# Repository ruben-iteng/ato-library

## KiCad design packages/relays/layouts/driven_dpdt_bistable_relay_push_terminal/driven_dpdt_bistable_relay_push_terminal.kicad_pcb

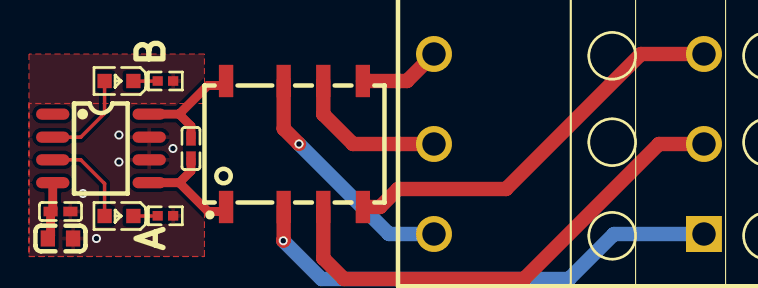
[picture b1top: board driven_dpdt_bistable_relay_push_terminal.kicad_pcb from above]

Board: 2 copper layers, 10 parts (0 on the bottom side), 14 nets.

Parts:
C1: 100nF ±10% 16V X7R; C0402
C2: 4.7µF ±10% 16V X5R; C0603
C3: 100pF ±5% 50V C0G; C0402
CN1: CONN-TH_KF250T-5.0-2X3P
LED1, LED2: LED0603-RD
R1, R2: 10kΩ ±1% 62.5mW; R0402
U1: SOP-8_L4.9-W3.9-P1.27-LS6.0-BL
U2: RELAY-SMD_G6KU-2F-Y

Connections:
OUTA: C3.1, U1.8, U2.8
anode: LED1.2, U1.2
anode-1: LED2.2, U1.3
cathode: LED1.1, R1.1
cathode-1: LED2.1, R2.1
gnd: C1.2, C2.2, R1.2, R2.2, U1.6, U1.7
hv: C1.1, C2.1, U1.4
line: CN1.3, U2.3
line-1: CN1.4, U2.6
line-2: CN1.1, U2.2
line-3: CN1.2, U2.7
line-4: CN1.5, U2.4
line-5: CN1.6, U2.5
relay-gnd: C3.2, U1.5, U2.1

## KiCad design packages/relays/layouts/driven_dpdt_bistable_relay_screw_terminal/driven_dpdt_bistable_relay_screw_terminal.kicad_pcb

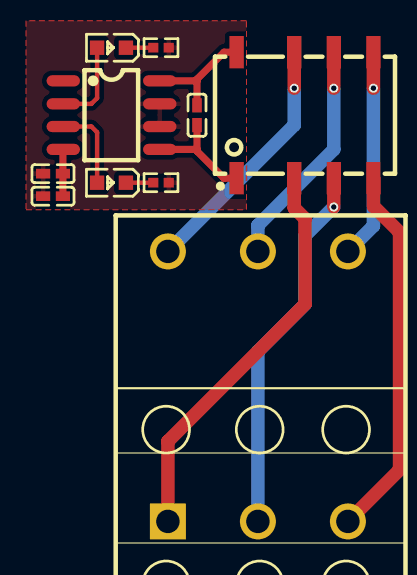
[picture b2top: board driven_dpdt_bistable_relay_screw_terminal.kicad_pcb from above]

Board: 2 copper layers, 10 parts (0 on the bottom side), 14 nets.

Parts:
C1, C2, C3: 100nF ±10% 16V X7R; C0402-b3ef17
D1, D2: LED0603-RD-c81ffb
R1, R2: 100kΩ ±1% 62.5mW; R0402-56259e
RELAY1: RELAY-SMD_G6KU-2F-Y-bd7654
U1: SOP-8_L4.9-W3.9-P1.27-LS6.0-BL-0d1ac6
X1: CONN-TH_KF250T-5.0-2X3P-058638

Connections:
PA1: RELAY1.2, X1.1
PA2: RELAY1.3, X1.3
PA3: RELAY1.4, X1.5
PB1: RELAY1.7, X1.2
PB2: RELAY1.6, X1.4
PB3: RELAY1.5, X1.6
gnd: C3.2, RELAY1.1, U1.5
gnd-1: C1.2, C2.2, R1.2, R2.2, U1.6, U1.7
hv: C3.1, RELAY1.8, U1.8
hv-1: C1.1, C2.1, U1.4
line: D1.2, U1.2
line-1: D2.2, U1.3
relay.led_indicator_a.led-cathode: D1.1, R1.1
relay.led_indicator_b.led-cathode: D2.1, R2.1

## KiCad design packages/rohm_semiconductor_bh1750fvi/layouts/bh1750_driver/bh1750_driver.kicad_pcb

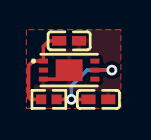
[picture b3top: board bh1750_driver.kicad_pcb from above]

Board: 2 copper layers, 4 parts (0 on the bottom side), 3 nets.

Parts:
C1, C2: 100nF ±10% 16V X7R; C0402
R1: 1kΩ ±1% 62.5mW; R0402
U1: WSOF-6_L2.6-W1.6-P0.50-TL-EP

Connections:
DVI: C2.1, R1.2, U1.5
VCC: C1.1, R1.1, U1.1
gnd: C1.2, C2.2, U1.3, U1.7

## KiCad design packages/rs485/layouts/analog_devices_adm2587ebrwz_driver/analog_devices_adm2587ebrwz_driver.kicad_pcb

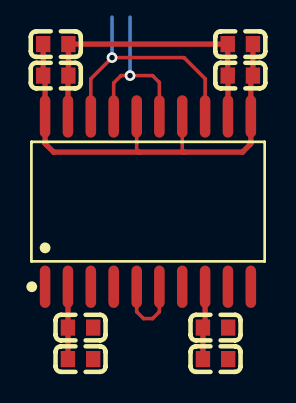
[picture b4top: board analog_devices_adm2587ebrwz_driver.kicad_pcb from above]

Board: 2 copper layers, 9 parts (0 on the bottom side), 7 nets.

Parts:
C1, C3, C5, C7: 100nF ±5% 50V X7R; C0603
C2, C4, C6, C8: 10nF ±5% 50V X7R; C0603
U1: SOIC-20_L13.0-W7.6-P1.27-LS10.3-BL

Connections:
gnd: C1.2, C2.2, C3.2, C4.2, U1.11, U1.14, U1.16, U1.20
gnd-1: C5.2, C6.2, C7.2, C8.2, U1.1, U1.3, U1.9, U1.10
hv: C1.1, C2.1, C3.1, C4.1, U1.12, U1.19
hv-1: C5.1, C6.1, C7.1, C8.1, U1.2, U1.8
line: U1.5, U1.6
line-1: U1.15, U1.17
line-2: U1.13, U1.18

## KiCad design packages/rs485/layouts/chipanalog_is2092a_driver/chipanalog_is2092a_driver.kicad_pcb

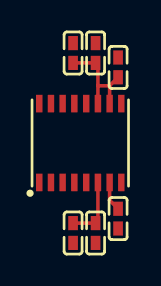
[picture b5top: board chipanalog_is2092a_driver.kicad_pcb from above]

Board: 2 copper layers, 7 parts (0 on the bottom side), 5 nets.

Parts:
C1, C2: 1µF ±10% 25V X5R; C0402
C3, C4: 10µF ±20% 6.3V X5R; C0402
C5, C6: 100nF ±10% 16V X7R; C0402
U1: LGA-16_L5.2-W4.7-P0.65-TL_CA-IS2062A-FRANK2

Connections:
VDDL: C1.1, U1.7
VDDP: C3.1, C5.1, U1.6
gnd: C1.2, C3.2, C5.2, U1.5, U1.8
gnd-1: C2.2, C4.2, C6.2, U1.9, U1.12
hv: C2.1, C4.1, C6.1, U1.10, U1.11

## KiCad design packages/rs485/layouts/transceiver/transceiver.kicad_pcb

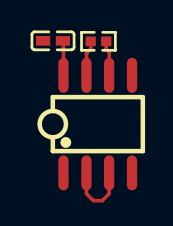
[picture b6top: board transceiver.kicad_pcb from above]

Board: 2 copper layers, 3 parts (0 on the bottom side), 5 nets.

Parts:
C1: 100nF ±10% 16V X7R; C0402-b3ef17
R1: 120Ω ±1% 62.5mW; R0402-56259e
U1: SOIC-8_L5.0-W4.0-P1.27-LS6.0-BL-294f77

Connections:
gnd: C1.2, U1.5
hv: C1.1, U1.8
line-2: R1.1, U1.6
line-3: R1.2, U1.7
line-4: U1.2, U1.3

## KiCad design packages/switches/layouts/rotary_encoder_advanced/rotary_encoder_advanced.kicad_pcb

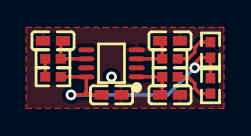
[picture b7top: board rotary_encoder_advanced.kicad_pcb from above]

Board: 2 copper layers, 11 parts (0 on the bottom side), 8 nets.

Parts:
C1, C2, C3, C4: 100nF ±10% 16V X7R; C0402
R1, R2, R3, R4, R5, R6: 10kΩ ±1% 62.5mW; R0402
U1: VSSOP-8_L2.3-W2.0-P0.50-LS3.1-BR

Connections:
a: R1.1, R4.1
b: R2.1, R5.1
gnd: C1.2, C2.2, C3.2, C4.2, U1.4
hv: C1.1, R1.2, R2.2, R3.2, U1.8
line-2: C2.1, R4.2, U1.1
line-3: C3.1, R5.2, U1.3
line-4: C4.1, R6.2, U1.6
switch: R3.1, R6.1
